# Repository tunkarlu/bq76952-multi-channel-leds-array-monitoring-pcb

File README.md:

# BQ76952 Multi-Channel LED Monitoring PCB

## How to Use This Repo
1. Clone or download the project and open `BQ76952_uPi_Hat.kicad_pro` with KiCad 8.x or newer.
2. Use the schematic (`.kicad_sch`) to inspect signal naming, channel scaling, and LM317 regulator settings; propagate changes into the PCB (`.kicad_pcb`) via KiCad's **Update PCB from Schematic** tool.
3. Generate fabrication outputs (Gerbers, drills, pick-and-place, and `BQ76952_uPi_Hat.csv`) when you are ready to order boards or run simulations for your experiments.
4. Document measurement runs and firmware configurations in your own branch to keep bachelor thesis logs aligned with the exact hardware revision.

## Purpose & Scope
This board is the hardware platform for a bachelor thesis focused on predicting high-power LED lifetime and scheduling preventative maintenance. It leverages Texas Instruments' `BQ76952` BMS front-end to acquire per-LED telemetry with up to 32-bit resolution, enabling precise degradation tracking for as many as 16 LEDs (down to 5 by shorting unused inputs). The design is intentionally scalable: multiple boards can share a single Raspberry Pi Zero host via SPI chip-select fan-out or operate independently over I2C.

## Hardware Highlights
- `BQ76952` monitors every LED string, providing ADC accuracy, protection, and internal diagnostics normally reserved for battery stacks.
- External LM317-based LDO supplies the Raspberry Pi Zero directly from the board; an additional comparator supervises the LDO output so a 5 V status indicator confirms the Pi rail is within tolerance.
- Status LEDs expose board health at a glance: chip power-on via the internal LDO, network OK, I2C OK, streaming OK, error flags, and 5 V OK from the comparator stage.
- 2.54 mm pitch Würth 20-pin connector handles the LED array interface with ample current capability and clear pin-1 orientation for field swaps.
- Mini DIP switch enables or disables immediate cloud streaming so field techs can start data uploads without reflashing firmware.
- Debug header breaks out key BQ76952 and Pi Zero signals to simplify firmware bring-up and probing.

## File Structure (Essential Only)
- `BQ76952_uPi_Hat.kicad_pro` – master KiCad project tying schematic, PCB, and fabrication settings together.
- `BQ76952_uPi_Hat.kicad_sch` – complete schematic including LED channels, LM317 LDO, comparator, DIP switch, and interface headers.
- `BQ76952_uPi_Hat.kicad_pcb` – board layout optimized for short sense paths and high-current connector routing.
- `BQ76952_uPi_Hat.csv` – bill of materials exported for sourcing and documentation.
- `BQ76952_uPi_Hat-backups/` – automatically generated KiCad backup snapshots for traceability between thesis milestones.

## Operating Modes & Scalability
- **LED Capacity**: Populate between 5 and 16 channels; unused inputs can be shorted to maintain ADC scaling without redesigning the board.
- **Host Interfaces**: Default communication relies on I2C, but SPI pads and separate slave-select lines allow one microprocessor to orchestrate two boards simultaneously.
- **Streaming Control**: Flip the dedicated DIP switch to trigger the firmware's cloud-streaming routine, useful when demonstrating predictive maintenance dashboards.
- **Resolution**: Each LED measurement path maintains up to 32 bits of resolution through firmware-side accumulation, helping extrapolate lumen depreciation trends.

## Bring-Up & Test Flow
1. Power the board from a current-limited supply, verify the BQ76952 internal LDO brings up the power-on indicator, and ensure the comparator asserts 5 V OK once the LM317 output settles.
2. Attach a Raspberry Pi Zero through the onboard connector, confirm I2C communication, then enable SPI if you plan to chain boards via different slave-select pins.
3. Toggle the DIP switch to start cloud streaming and observe the network and streaming indicators before connecting real LED loads.
4. Connect LED strings incrementally, watching each status LED and reading diagnostic registers to confirm per-channel integrity.
5. Use the debug header to probe GPIOs or update firmware while recording data for the thesis lifetime-prediction models.

## Thesis Context
The design forms the experimental backbone for a bachelor thesis investigating predictive maintenance of high-power LED arrays. It demonstrates how a BMS-grade analog front-end, auxiliary regulation, and human-friendly status cues can be repurposed into a scalable monitoring platform suitable for lab studies and eventual field deployments.

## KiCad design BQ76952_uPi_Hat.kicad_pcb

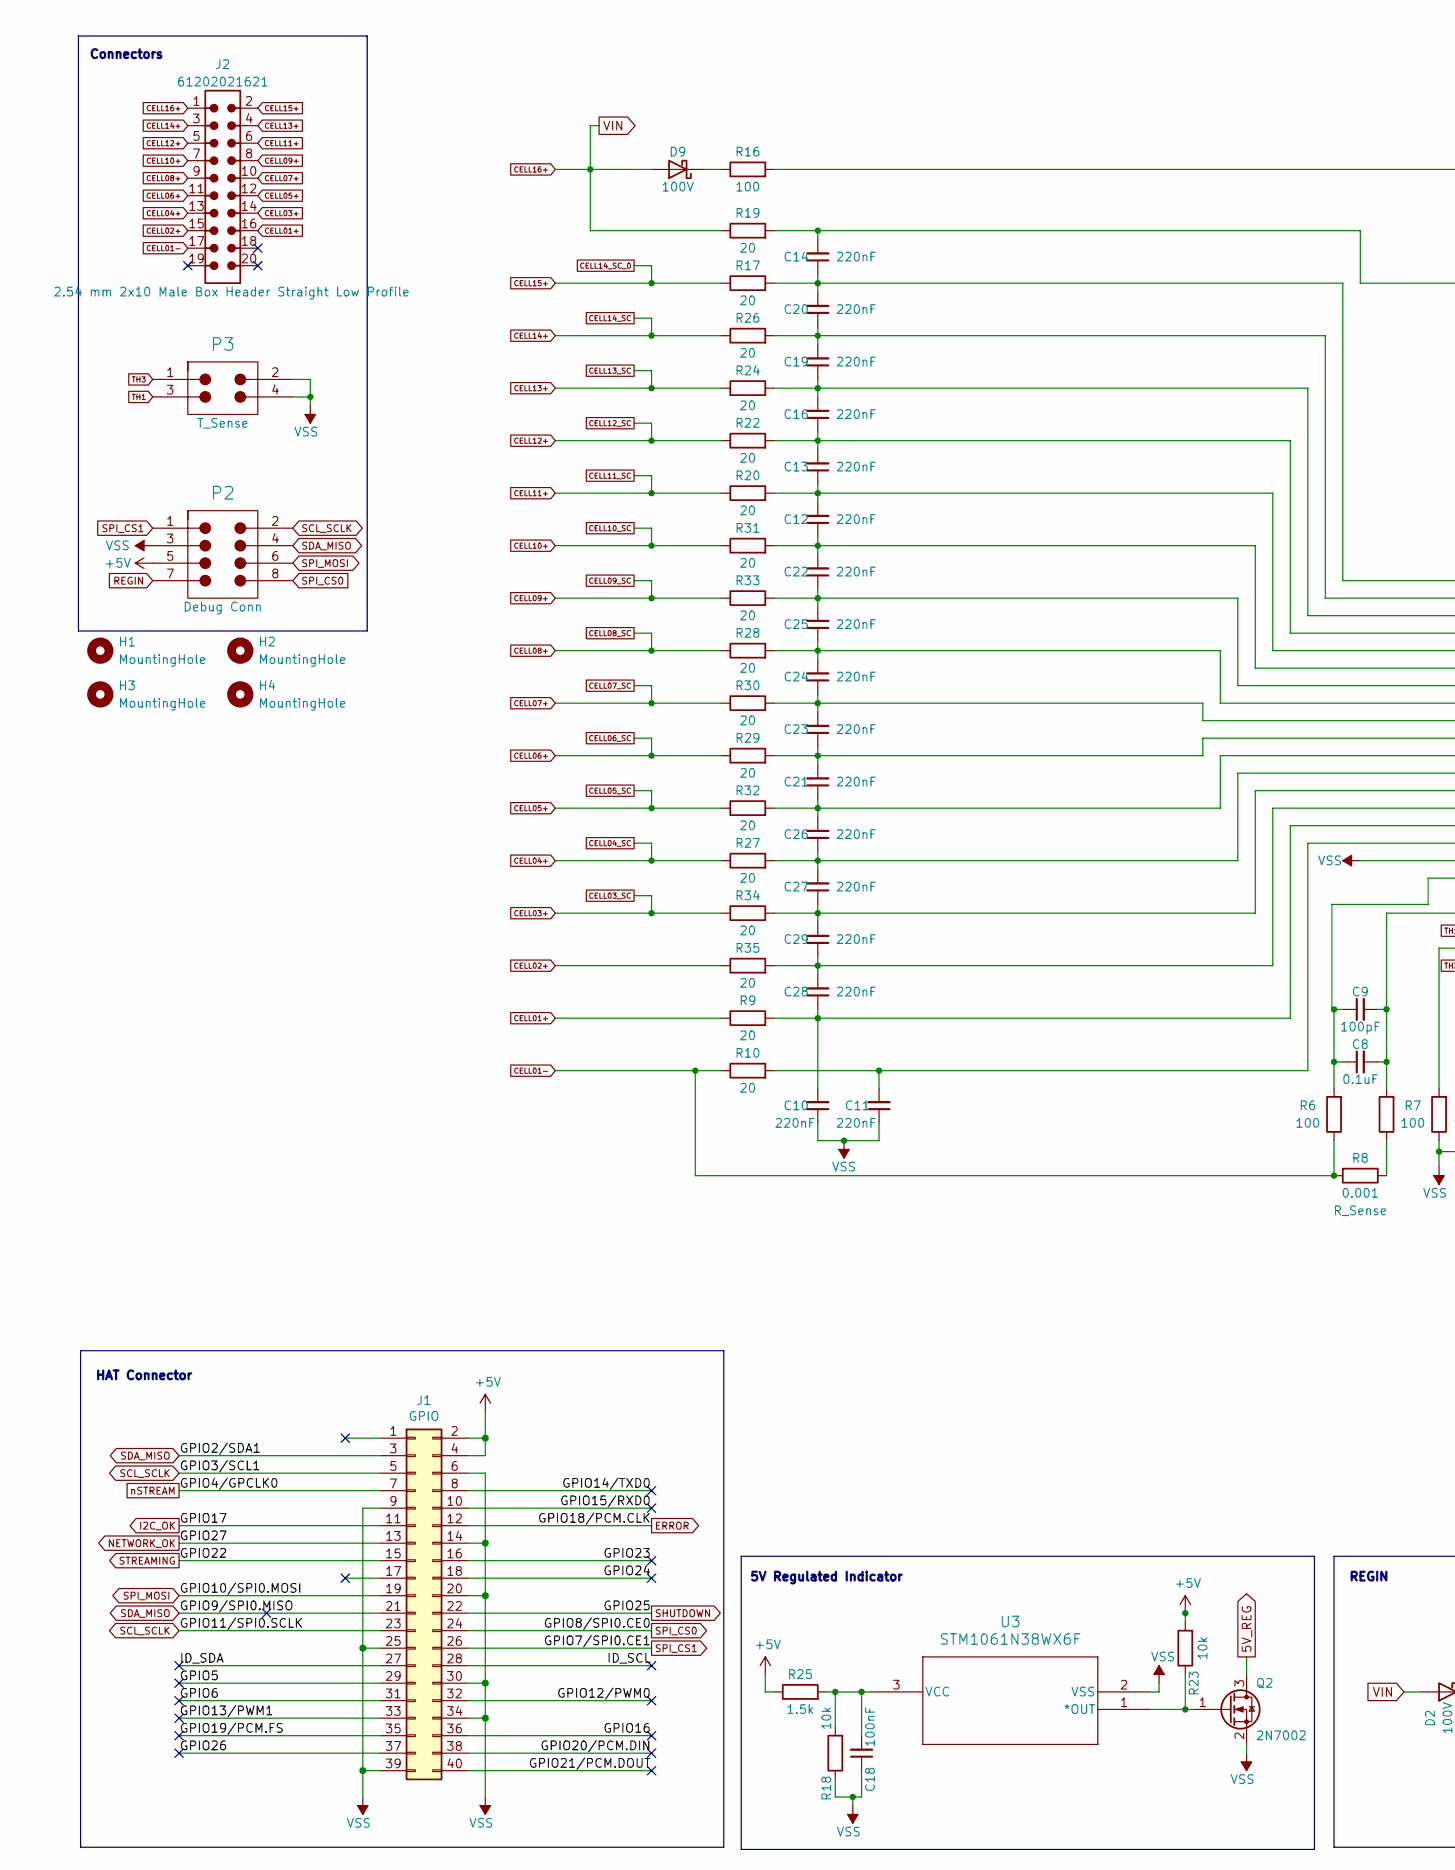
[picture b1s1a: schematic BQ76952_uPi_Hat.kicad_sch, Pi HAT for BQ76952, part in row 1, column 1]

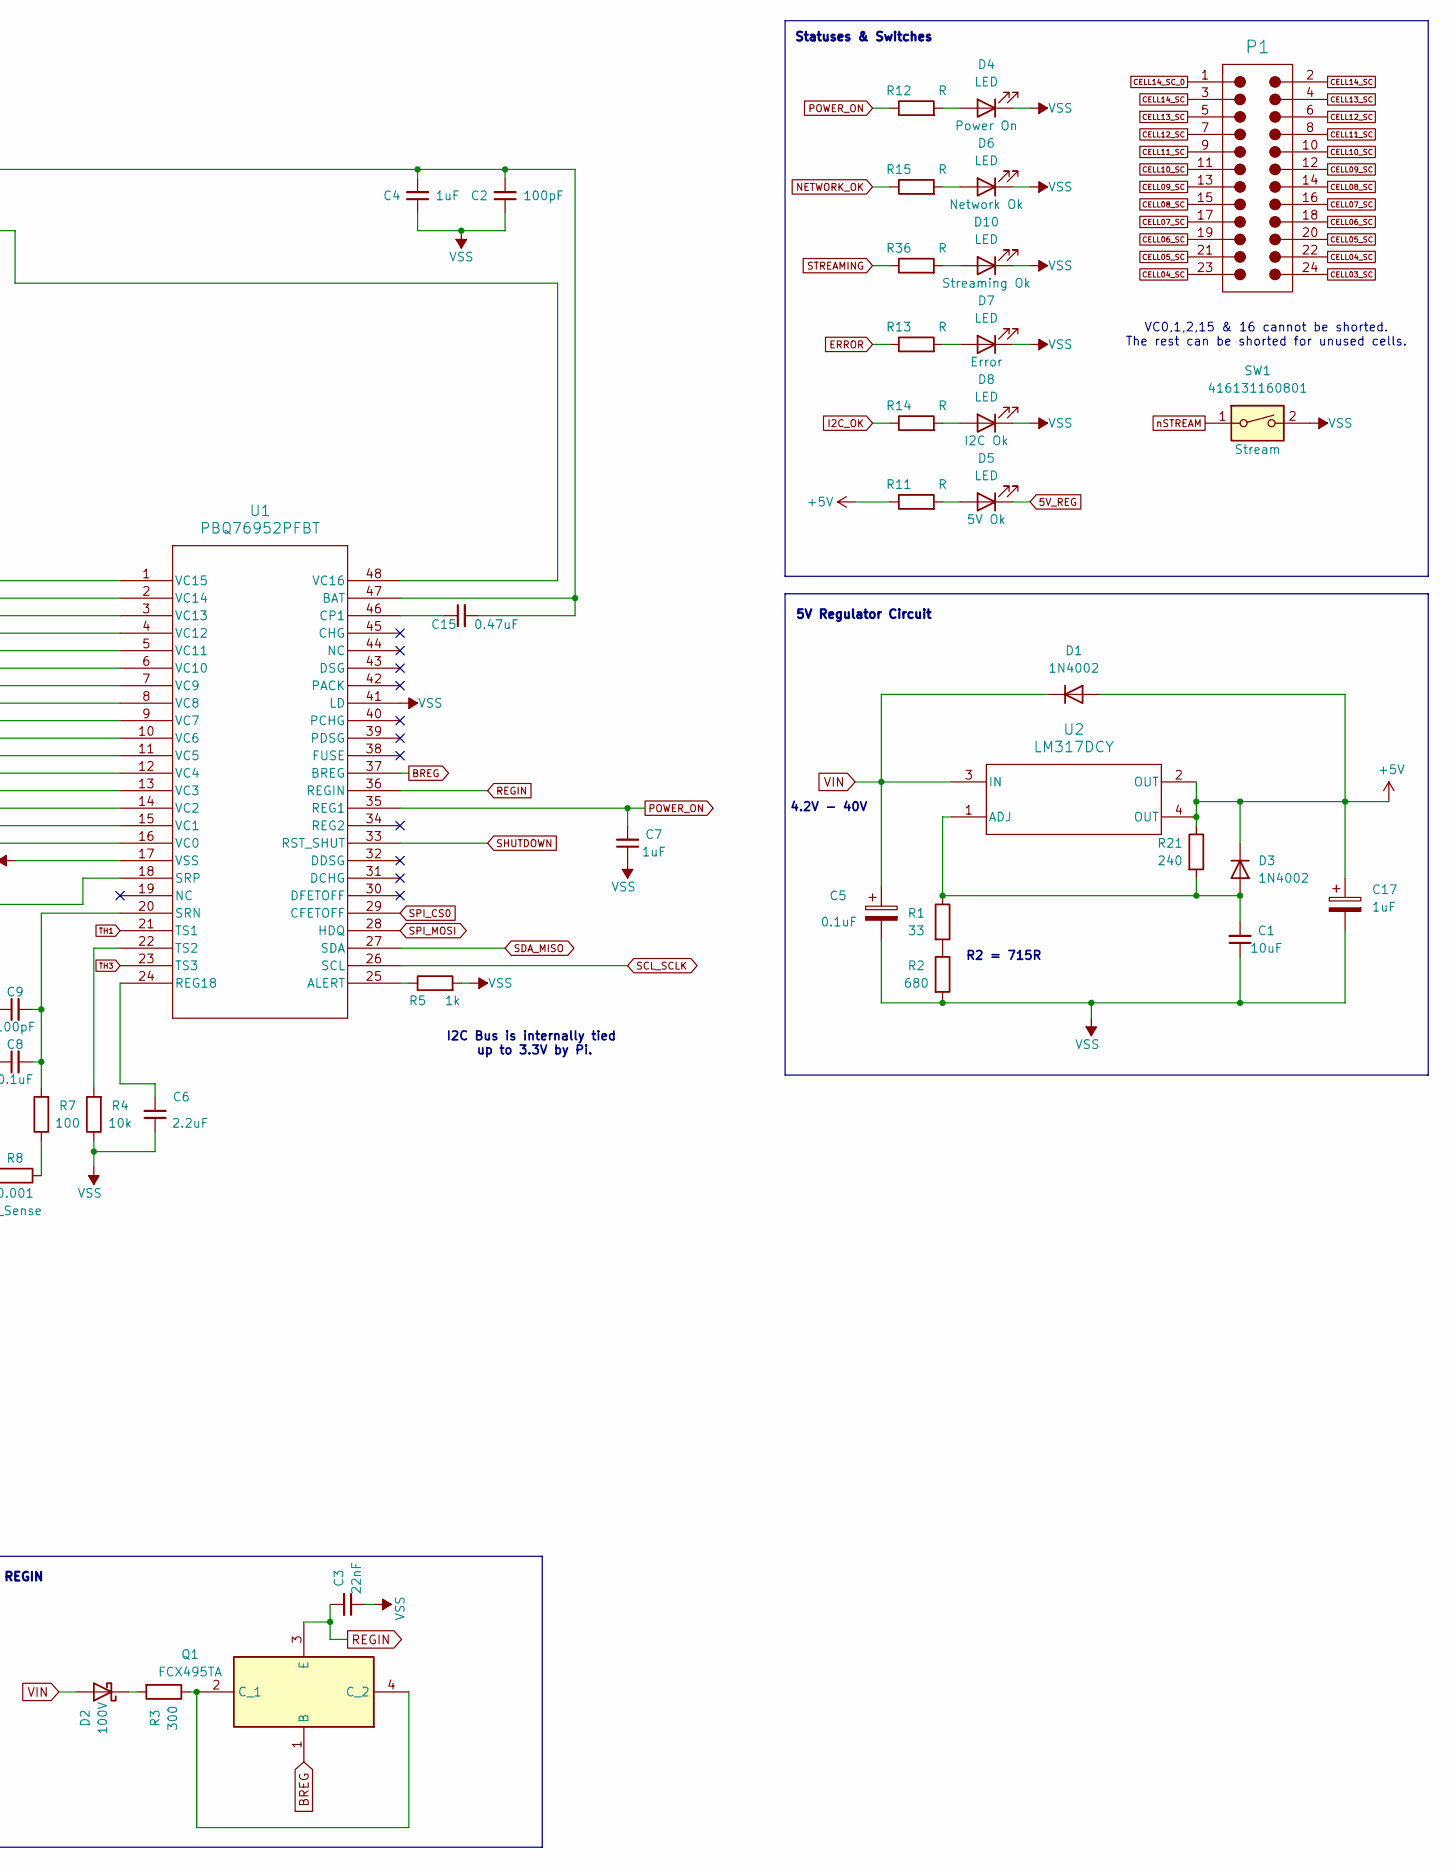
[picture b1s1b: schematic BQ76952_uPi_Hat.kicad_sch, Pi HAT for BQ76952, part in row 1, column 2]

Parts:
C1: 10uF; C_0805_2012Metric_Pad1.18x1.45mm_HandSolder
C2, C9: 100pF; C_0805_2012Metric_Pad1.18x1.45mm_HandSolder
C3: 22nF; C_0805_2012Metric_Pad1.18x1.45mm_HandSolder
C4, C7: 1uF; C_0805_2012Metric_Pad1.18x1.45mm_HandSolder
C5: 0.1uF; C_0805_2012Metric
C6: 2.2uF; C_0805_2012Metric_Pad1.18x1.45mm_HandSolder
C8: 0.1uF; C_0805_2012Metric_Pad1.18x1.45mm_HandSolder
C10, C11, C12, C13, C14, C16, C19, C20, C21, C22, C23, C24, C25, C26, C27, C28, C29: 220nF; C_0805_2012Metric_Pad1.18x1.45mm_HandSolder
C15: 0.47uF; C_0805_2012Metric_Pad1.18x1.45mm_HandSolder
C17: 1uF; C_0805_2012Metric
C18: 100nF; C_0805_2012Metric_Pad1.18x1.45mm_HandSolder
D1, D3: 1N4002; D_SMA_Handsoldering
D2, D9: 100V; D_SMA
D4, D5, D6, D7, D8, D10: LED; LED_0805_2012Metric_Pad1.15x1.40mm_HandSolder
H1, H2, H3, H4: MountingHole; MountingHole_2.7mm_M2.5_DIN965
J1: GPIO; PinSocket_2x20_P2.54mm_Vertical_Inverted
J2: 61202021621; J_Wurth_WR-BHD_61202021621
P1: 61302421121; Working Voltage 250V; Withstanding Voltage 500V; Manufacturer Part Number 61302421121
P2: 61300821121; Working Voltage 250V; Withstanding Voltage 500V; Manufacturer Part Number 61300821121
P3: 61300421121; Working Voltage 250V; Withstanding Voltage 500V; Manufacturer Part Number 61300421121
Q1: FCX495TA; FCX495QTA; Mouser Part Number 522-FCX495TA
Q2: 2N7002; SOT-23
R1: 33; R_0805_2012Metric_Pad1.20x1.40mm_HandSolder
R2: 680; R_0805_2012Metric_Pad1.20x1.40mm_HandSolder
R3: 300; R_0805_2012Metric_Pad1.20x1.40mm_HandSolder
R4, R18, R23: 10k; R_0805_2012Metric_Pad1.20x1.40mm_HandSolder
R5: 1k; R_0805_2012Metric_Pad1.20x1.40mm_HandSolder
R6, R7, R16: 100; R_0805_2012Metric_Pad1.20x1.40mm_HandSolder
R8: 0.001; R_0805_2012Metric_Pad1.20x1.40mm_HandSolder
R9, R10, R17, R19, R20, R22, R24, R26, R27, R28, R29, R30, R31, R32, R33, R34, R35: 20; R_0805_2012Metric_Pad1.20x1.40mm_HandSolder
R11, R12, R13, R14, R15, R36: R; R_0805_2012Metric_Pad1.20x1.40mm_HandSolder
R21: 240; R_0805_2012Metric_Pad1.20x1.40mm_HandSolder
R25: 1.5k; R_0805_2012Metric_Pad1.20x1.40mm_HandSolder
SW1: 416131160801
U1: PBQ76952PFBT; PFB48_TEX
U2: LM317DCY; DCY0004A_N
U3: STM1061N38WX6F; SOT-23_STM

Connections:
5V_REG: D5.1 (K), Q2.3 (D)
+5V: C17.1, D1.2 (A), D3.1 (K), J1.2, J1.4, P2.5, R11.1, R21.1, R23.2, R25.1, U2.2 (OUT), U2.4 (OUT)
/GPIO5: J1.29
/GPIO6: J1.31
/GPIO12/PWM0: J1.32
/GPIO13/PWM1: J1.33
/GPIO14/TXD0: J1.8
/GPIO15/RXD0: J1.10
/GPIO16: J1.36
/GPIO19/PCM.FS: J1.35
/GPIO20/PCM.DIN: J1.38
/GPIO21/PCM.DOUT: J1.40
/GPIO23: J1.16
/GPIO24: J1.18
/GPIO26: J1.37
/ID_SCL: J1.28
/ID_SDA: J1.27
BREG: Q1.1 (B), U1.37 (BREG)
CELL01+: J2.16, R9.1
CELL01-: J2.17, R6.1, R8.2, R10.1
CELL02+: J2.15, R35.1
CELL03+: J2.14, P1.24, R34.1
CELL04+: J2.13, P1.22, P1.23, R27.1
CELL05+: J2.12, P1.20, P1.21, R32.1
CELL06+: J2.11, P1.18, P1.19, R29.1
CELL07+: J2.10, P1.16, P1.17, R30.1
CELL08+: J2.9, P1.14, P1.15, R28.1
CELL09+: J2.8, P1.12, P1.13, R33.1
CELL10+: J2.7, P1.10, P1.11, R31.1
CELL11+: J2.6, P1.8, P1.9, R20.1
CELL12+: J2.5, P1.6, P1.7, R22.1
CELL13+: J2.4, P1.4, P1.5, R24.1
CELL14+: J2.3, P1.2, P1.3, R26.1
CELL14_SC_0: J2.2, P1.1, R17.1
CELL16+: C5.1, D1.1 (K), D2.2 (A), D9.2 (A), J2.1, R19.1, U2.3 (IN)
ERROR: J1.12, R13.1
I2C_OK: J1.11, R14.1
NETWORK_OK: J1.13, R15.1
unnamed: D9.1 (K), R16.1
unnamed: D4.2 (A), R12.2
unnamed: D6.2 (A), R15.2
unnamed: D10.2 (A), R36.2
unnamed: D7.2 (A), R13.2
unnamed: D2.1 (K), R3.2
unnamed: C1.2, D3.2 (A), R1.1, R21.2, U2.1 (ADJ)
unnamed: D8.2 (A), R14.2
unnamed: D5.2 (A), R11.2
unnamed: Q1.2 (C_1), Q1.4 (C_2), R3.1
unnamed: Q2.1 (G), R23.1, U3.1 (*OUT)
unnamed: R7.1, R8.1
unnamed: R1.2, R2.1
unnamed: R5.1, U1.25 (ALERT)
unnamed: C2.2, C4.2, C15.2, R16.2, U1.47 (BAT)
unnamed: C15.1, U1.46 (CP1)
unnamed: C6.2, U1.24 (REG18)
unnamed: C8.2, C9.2, R7.2, U1.20 (SRN)
unnamed: C8.1, C9.1, R6.2, U1.18 (SRP)
unnamed: R4.2, U1.22 (TS2)
unnamed: C11.2, R10.2, U1.16 (VC0)
unnamed: C10.2, C28.1, R9.2, U1.15 (VC1)
unnamed: C28.2, C29.1, R35.2, U1.14 (VC2)
unnamed: C27.1, C29.2, R34.2, U1.13 (VC3)
unnamed: C26.1, C27.2, R27.2, U1.12 (VC4)
unnamed: C21.1, C26.2, R32.2, U1.11 (VC5)
unnamed: C21.2, C23.1, R29.2, U1.10 (VC6)
unnamed: C23.2, C24.1, R30.2, U1.9 (VC7)
unnamed: C24.2, C25.1, R28.2, U1.8 (VC8)
unnamed: C22.1, C25.2, R33.2, U1.7 (VC9)
unnamed: C12.1, C22.2, R31.2, U1.6 (VC10)
unnamed: C12.2, C13.1, R20.2, U1.5 (VC11)
unnamed: C13.2, C16.1, R22.2, U1.4 (VC12)
unnamed: C16.2, C19.1, R24.2, U1.3 (VC13)
unnamed: C19.2, C20.1, R26.2, U1.2 (VC14)
unnamed: C14.1, C20.2, R17.2, U1.1 (VC15)
unnamed: C14.2, R19.2, U1.48 (VC16)
unnamed: C18.2, R18.2, R25.2, U3.3 (VCC)
POWER_ON: C7.2, R12.1, U1.35 (REG1)
REGIN: C3.2, P2.7, Q1.3 (E), U1.36 (REGIN)
SCL_SCLK: J1.5, J1.23, P2.2, U1.26 (SCL)
SDA_MISO: J1.3, J1.21, P2.4, U1.27 (SDA)
SHUTDOWN: J1.22, U1.33 (RST_SHUT)
SPI_CS0: J1.24, P2.8, U1.29 (CFETOFF)
SPI_CS1: J1.26, P2.1
SPI_MOSI: J1.19, P2.6, U1.28 (HDQ)
STREAMING: J1.15, R36.1
TH1: P3.3, U1.21 (TS1)
TH3: P3.1, U1.23 (TS3)
VSS: C1.1, C2.1, C3.1, C4.1, C5.2, C6.1, C7.1, C10.1, C11.1, C17.2, C18.1, D4.1 (K), D6.1 (K), D7.1 (K), D8.1 (K), D10.1 (K), J1.6, J1.9, J1.14, J1.20, J1.25, J1.30, J1.34, J1.39, P2.3, P3.2, P3.4, Q2.2 (S), R2.2, R4.1, R5.2, R18.1, SW1.2, U1.17 (VSS), U1.41 (LD), U3.2 (VSS)
nSTREAM: J1.7, SW1.1

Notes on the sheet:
4.2V - 40V
HAT Connector
R2 = 715R
5V Regulator Circuit
Connectors
5V Regulated Indicator
I2C Bus is internally tied up to 3.3V by Pi.
Statuses & Switches
VC0,1,2,15 & 16 cannot be shorted. The rest can be shorted for unused cells.
REGIN

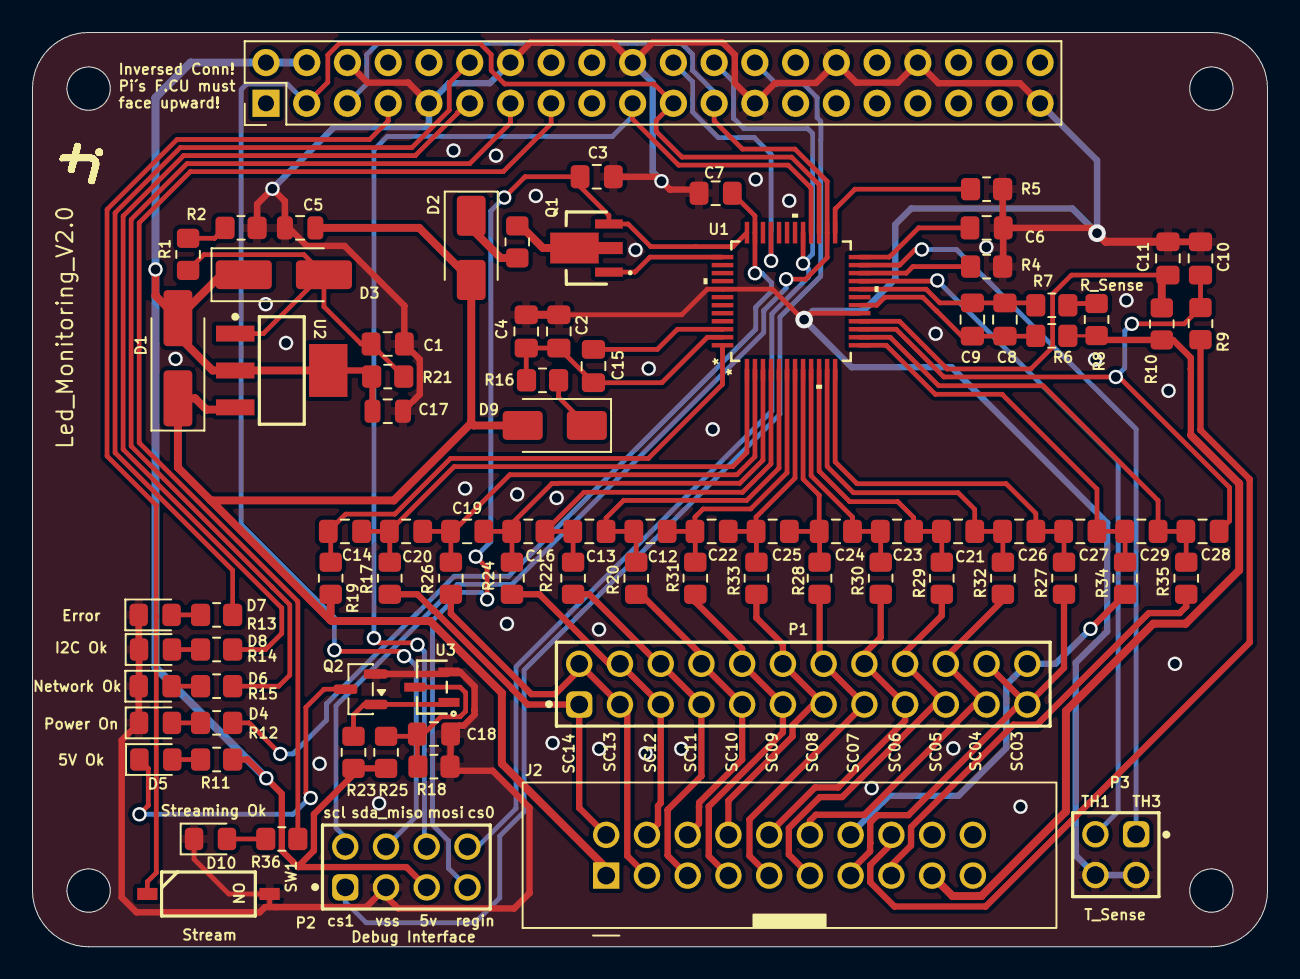
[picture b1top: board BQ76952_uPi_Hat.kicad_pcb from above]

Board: 2 copper layers, 77.0 x 57.0 mm, 90 parts (0 on the bottom side), 74 nets.

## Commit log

2026-02-04 pdf file out of date
2026-02-04 updating outdating files
2026-02-04 Update README with project setup instructions and image
    Added an image and improved instructions for project setup.
2026-02-04 host name update
2026-02-04 Clarify instructions for fabrication outputs
    Updated instructions for generating fabrication outputs.
2026-02-04 Update license from MIT to Apache 2.0
    Replaced MIT License with Apache License 2.0.
